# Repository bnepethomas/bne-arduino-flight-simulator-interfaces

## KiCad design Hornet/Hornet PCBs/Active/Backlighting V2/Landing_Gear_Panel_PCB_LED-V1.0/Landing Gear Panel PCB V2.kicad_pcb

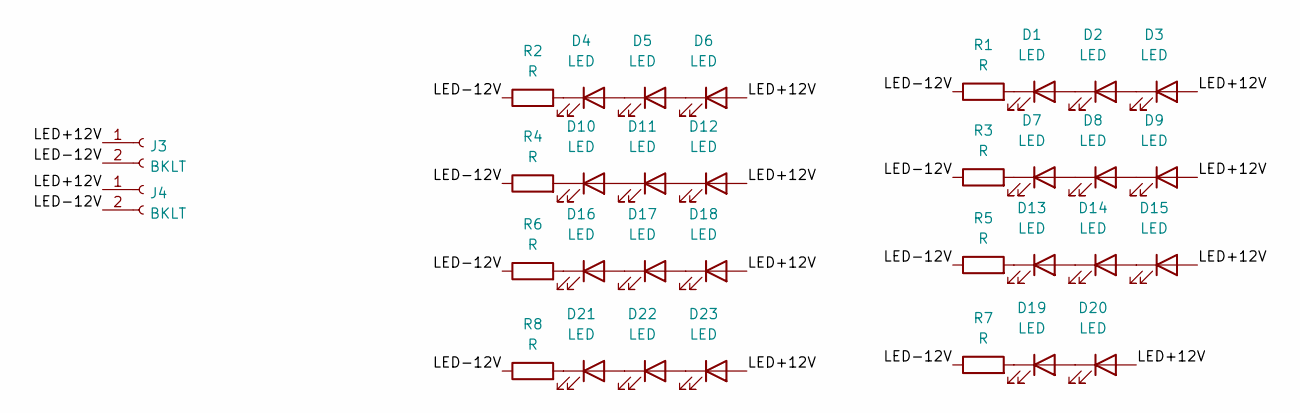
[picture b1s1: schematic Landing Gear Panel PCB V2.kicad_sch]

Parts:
D1, D2, D3, D4, D5, D6, D7, D8, D9, D10, D11, D12, D13, D14, D15, D16, D17, D18, D19, D20, D21, D22, D23: LED; LED_D3.0mm
J3, J4: BKLT; Molex_KK-254_AE-6410-02A_1x02_P2.54mm_Vertical
R1, R2, R3, R4, R5, R6, R7, R8: R; R_Axial_DIN0204_L3.6mm_D1.6mm_P2.54mm_Vertical

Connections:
/LED+12V: D3.2 (A), D6.2 (A), D9.2 (A), D12.2 (A), D15.2 (A), D18.2 (A), D20.2 (A), D23.2 (A), J3.1, J4.1
/LED-12V: J3.2, J4.2, R1.1, R2.1, R3.1, R4.1, R5.1, R6.1, R7.1, R8.1
unnamed: D1.1 (K), R1.2
unnamed: D1.2 (A), D2.1 (K)
unnamed: D2.2 (A), D3.1 (K)
unnamed: D4.1 (K), R2.2
unnamed: D4.2 (A), D5.1 (K)
unnamed: D5.2 (A), D6.1 (K)
unnamed: D7.1 (K), R3.2
unnamed: D7.2 (A), D8.1 (K)
unnamed: D8.2 (A), D9.1 (K)
unnamed: D10.1 (K), R4.2
unnamed: D10.2 (A), D11.1 (K)
unnamed: D11.2 (A), D12.1 (K)
unnamed: D13.1 (K), R5.2
unnamed: D13.2 (A), D14.1 (K)
unnamed: D14.2 (A), D15.1 (K)
unnamed: D16.1 (K), R6.2
unnamed: D16.2 (A), D17.1 (K)
unnamed: D17.2 (A), D18.1 (K)
unnamed: D19.1 (K), R7.2
unnamed: D19.2 (A), D20.1 (K)
unnamed: D21.1 (K), R8.2
unnamed: D21.2 (A), D22.1 (K)
unnamed: D22.2 (A), D23.1 (K)

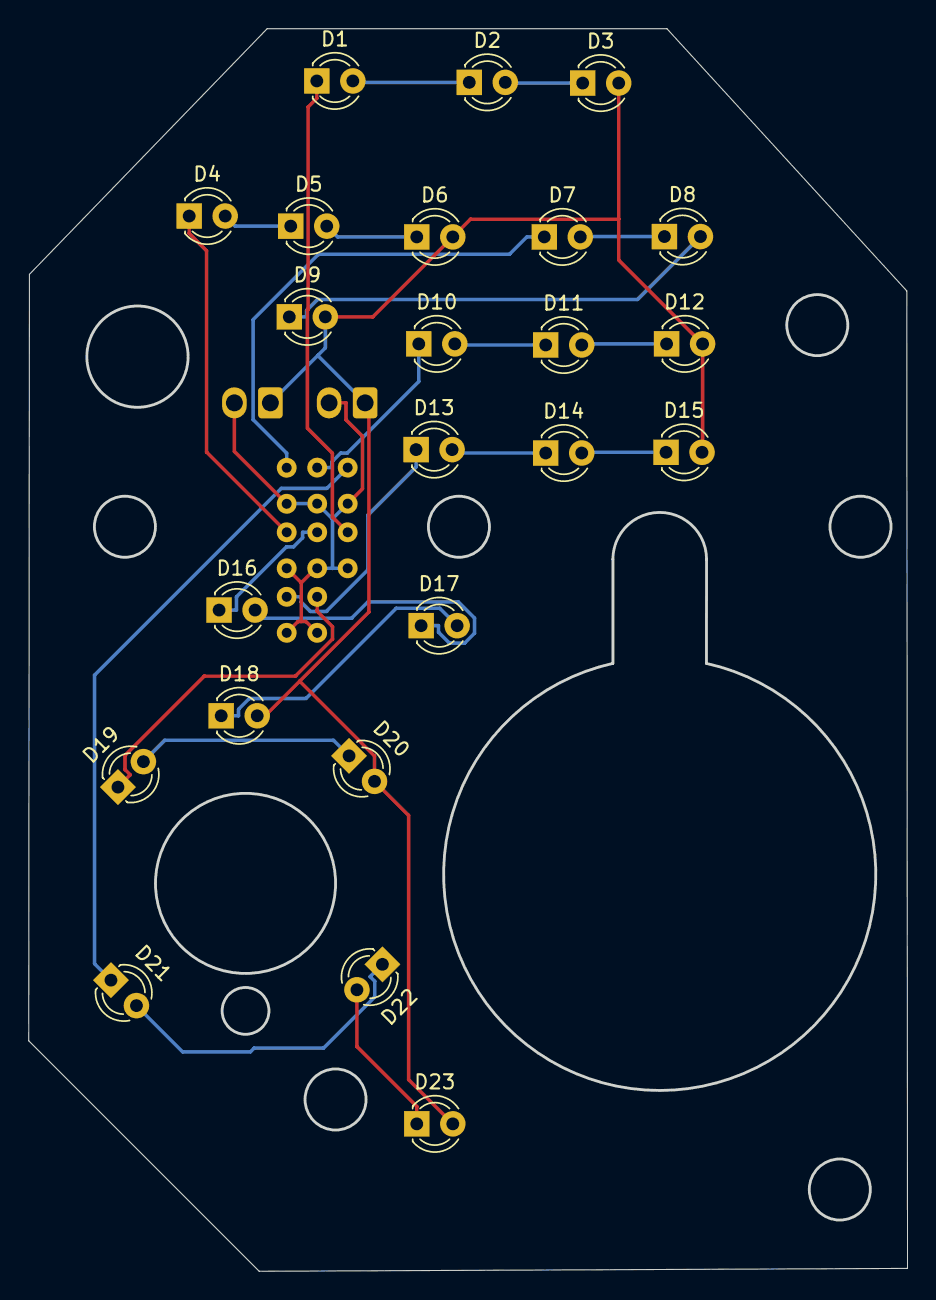
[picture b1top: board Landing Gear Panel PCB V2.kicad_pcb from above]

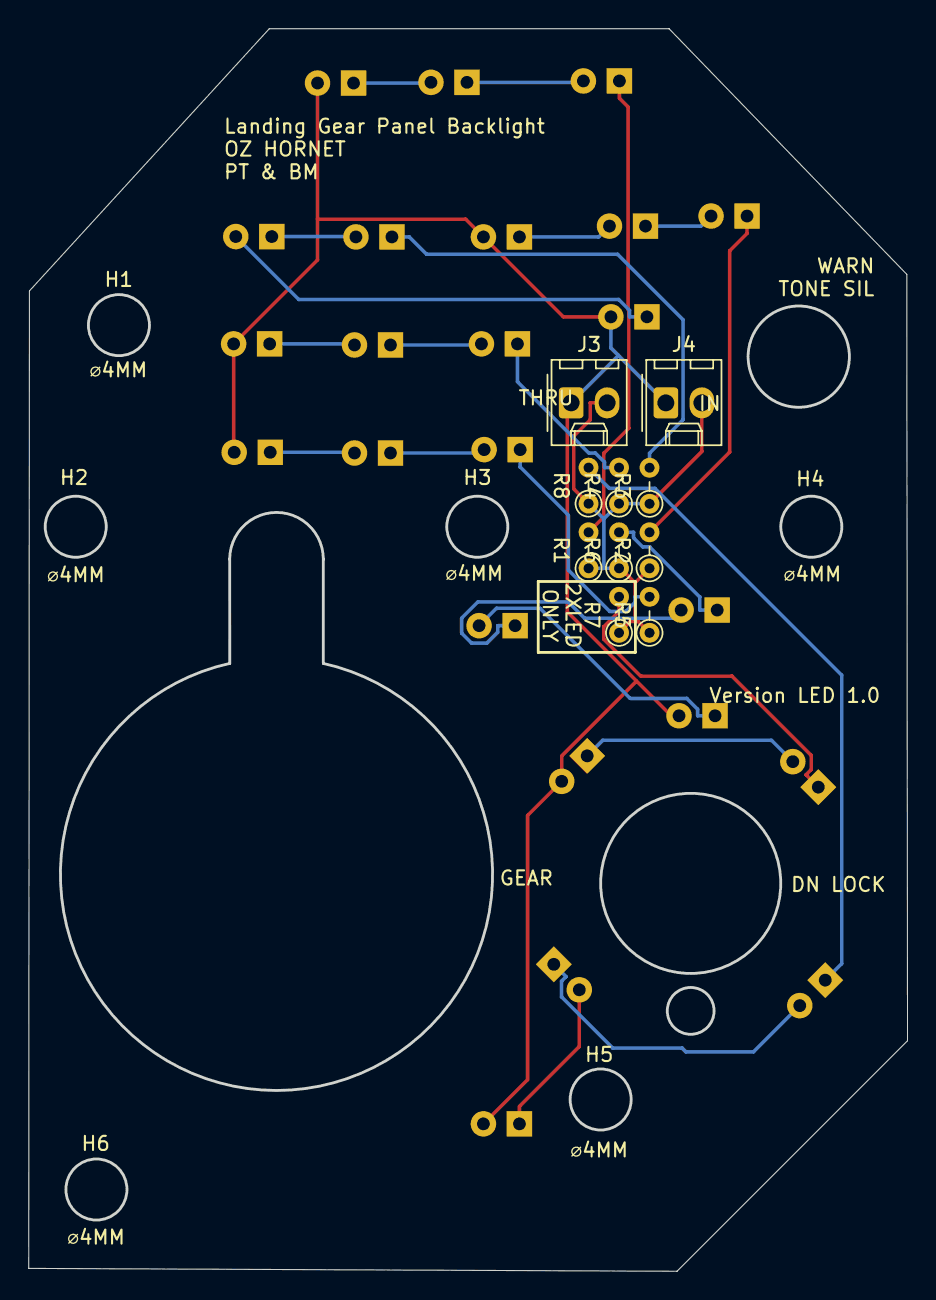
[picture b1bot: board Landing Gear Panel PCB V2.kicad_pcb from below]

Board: 2 copper layers, 62.0 x 87.6 mm, 33 parts (10 on the bottom side), 25 nets.

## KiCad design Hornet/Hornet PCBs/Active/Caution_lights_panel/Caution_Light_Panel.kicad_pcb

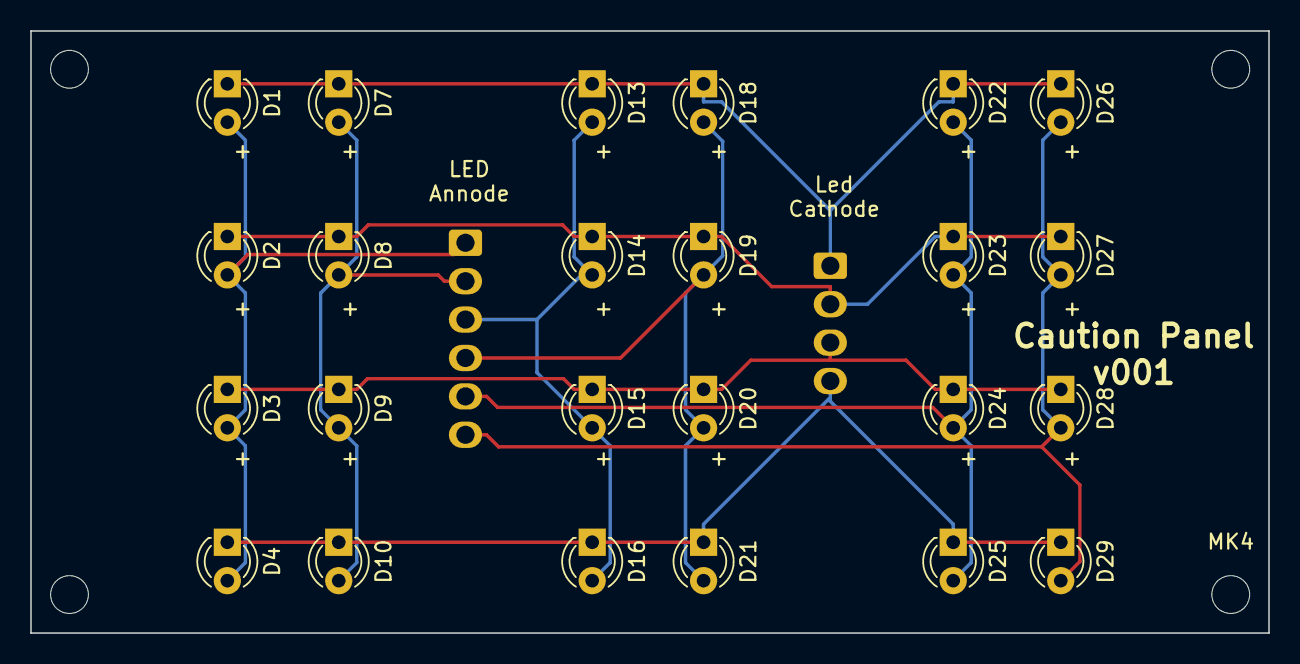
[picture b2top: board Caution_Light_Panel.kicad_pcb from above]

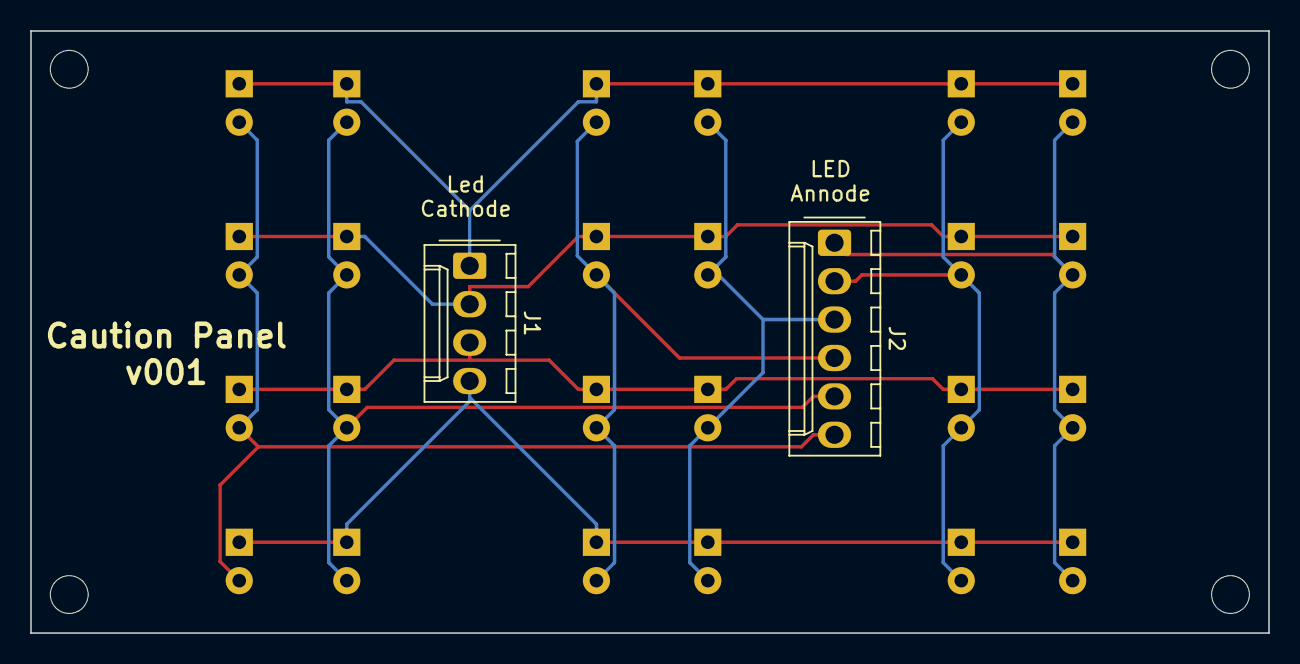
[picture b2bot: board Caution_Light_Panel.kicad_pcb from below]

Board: 2 copper layers, 81.9 x 39.8 mm, 30 parts (2 on the bottom side), 10 nets.

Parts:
D1: 0,0; LED_D3.0mm_FlatTop
D2: 1,0; LED_D3.0mm_FlatTop
D3: 2,0; LED_D3.0mm_FlatTop
D4: 3,0; LED_D3.0mm_FlatTop
D7: 0,1; LED_D3.0mm_FlatTop
D8: 1,1; LED_D3.0mm_FlatTop
D9: 2,1; LED_D3.0mm_FlatTop
D10: 3,1; LED_D3.0mm_FlatTop
D13: 0,2; LED_D3.0mm_FlatTop
D14: 1,2; LED_D3.0mm_FlatTop
D15: 2,2; LED_D3.0mm_FlatTop
D16: 3,2; LED_D3.0mm_FlatTop
D18: 0,3; LED_D3.0mm_FlatTop
D19: 1.3; LED_D3.0mm_FlatTop
D20: 2,3; LED_D3.0mm_FlatTop
D21: 3,3; LED_D3.0mm_FlatTop
D22: 0.4; LED_D3.0mm_FlatTop
D23: 1.4; LED_D3.0mm_FlatTop
D24: 2,4; LED_D3.0mm_FlatTop
D25: 3,4; LED_D3.0mm_FlatTop
D26: 0.5; LED_D3.0mm_FlatTop
D27: 1.5; LED_D3.0mm_FlatTop
D28: 2,5; LED_D3.0mm_FlatTop
D29: 3,5; LED_D3.0mm_FlatTop
J1: LedCathode; Molex_1x04_P2.54mm_Vertical
J2: LEDAnnode; Molex_1x06_P2.54mm_Vertical
MK1, MK2, MK3, MK4: Mounting_Hole; MountingHole_2.5mm

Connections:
/Dig0: D1.1, D7.1, D13.1, D18.1, D22.1, D26.1, J1.1
/Dig1: D2.1, D8.1, D14.1, D19.1, D23.1, D27.1, J1.2
/Dig2: D3.1, D9.1, D15.1, D20.1, D24.1, D28.1, J1.3
/Dig3: D4.1, D10.1, D16.1, D21.1, D25.1, D29.1, J1.4
/SegA: D7.2, D8.2, D9.2, D10.2, J2.2
/SegB: D13.2, D14.2, D15.2, D16.2, J2.3
/SegC: D18.2, D19.2, D20.2, D21.2, J2.4
/SegD: D22.2, D23.2, D24.2, D25.2, J2.5
/SegDP: D1.2, D2.2, D3.2, D4.2, J2.1
/SegE: D26.2, D27.2, D28.2, D29.2, J2.6

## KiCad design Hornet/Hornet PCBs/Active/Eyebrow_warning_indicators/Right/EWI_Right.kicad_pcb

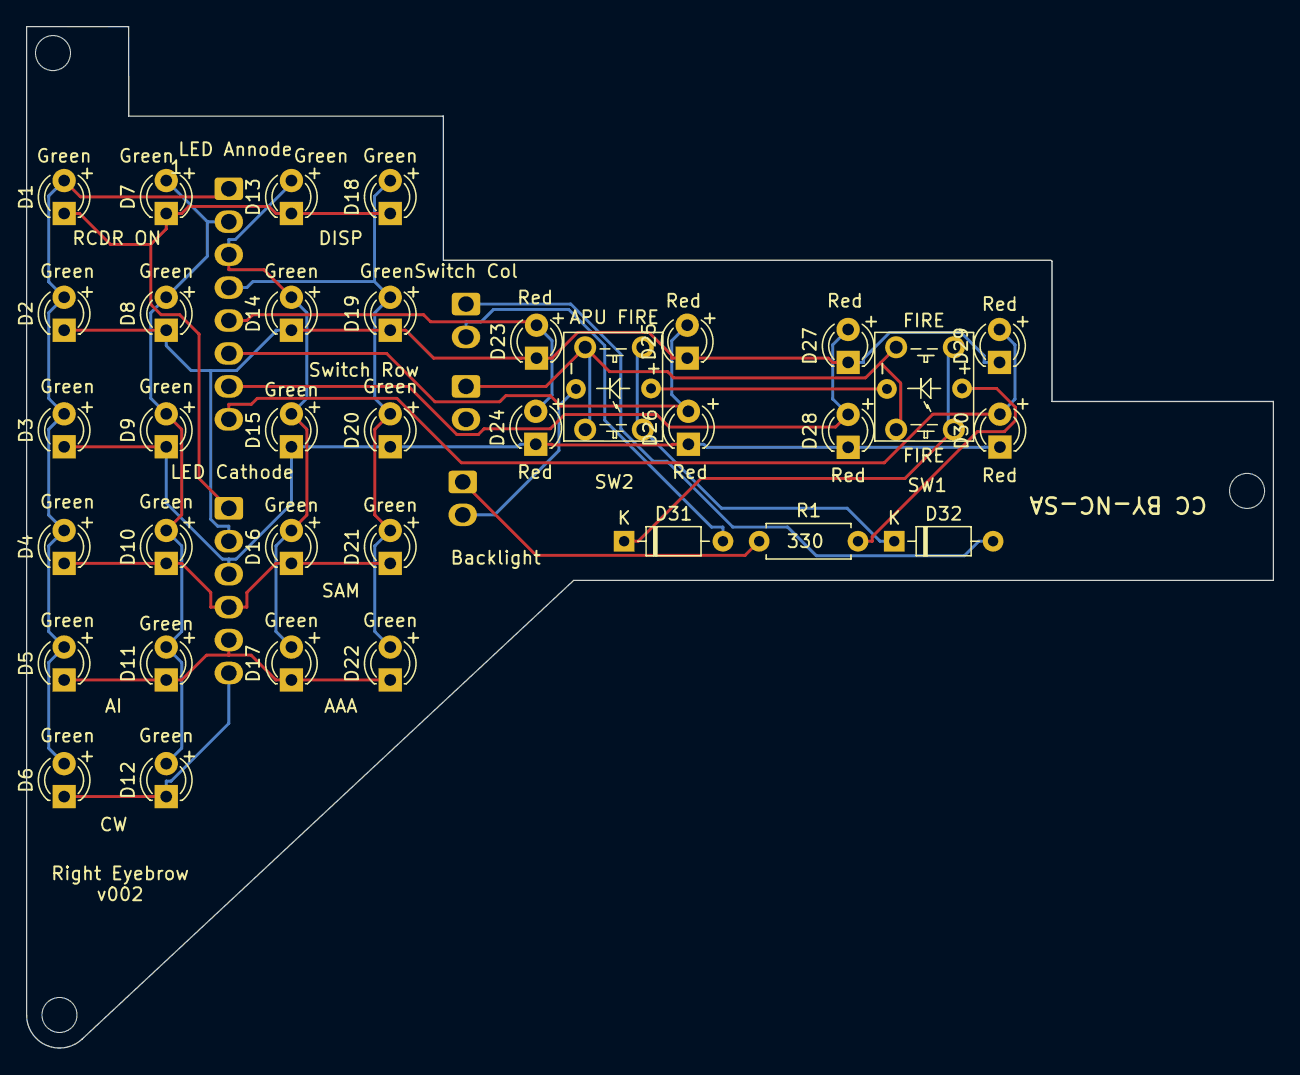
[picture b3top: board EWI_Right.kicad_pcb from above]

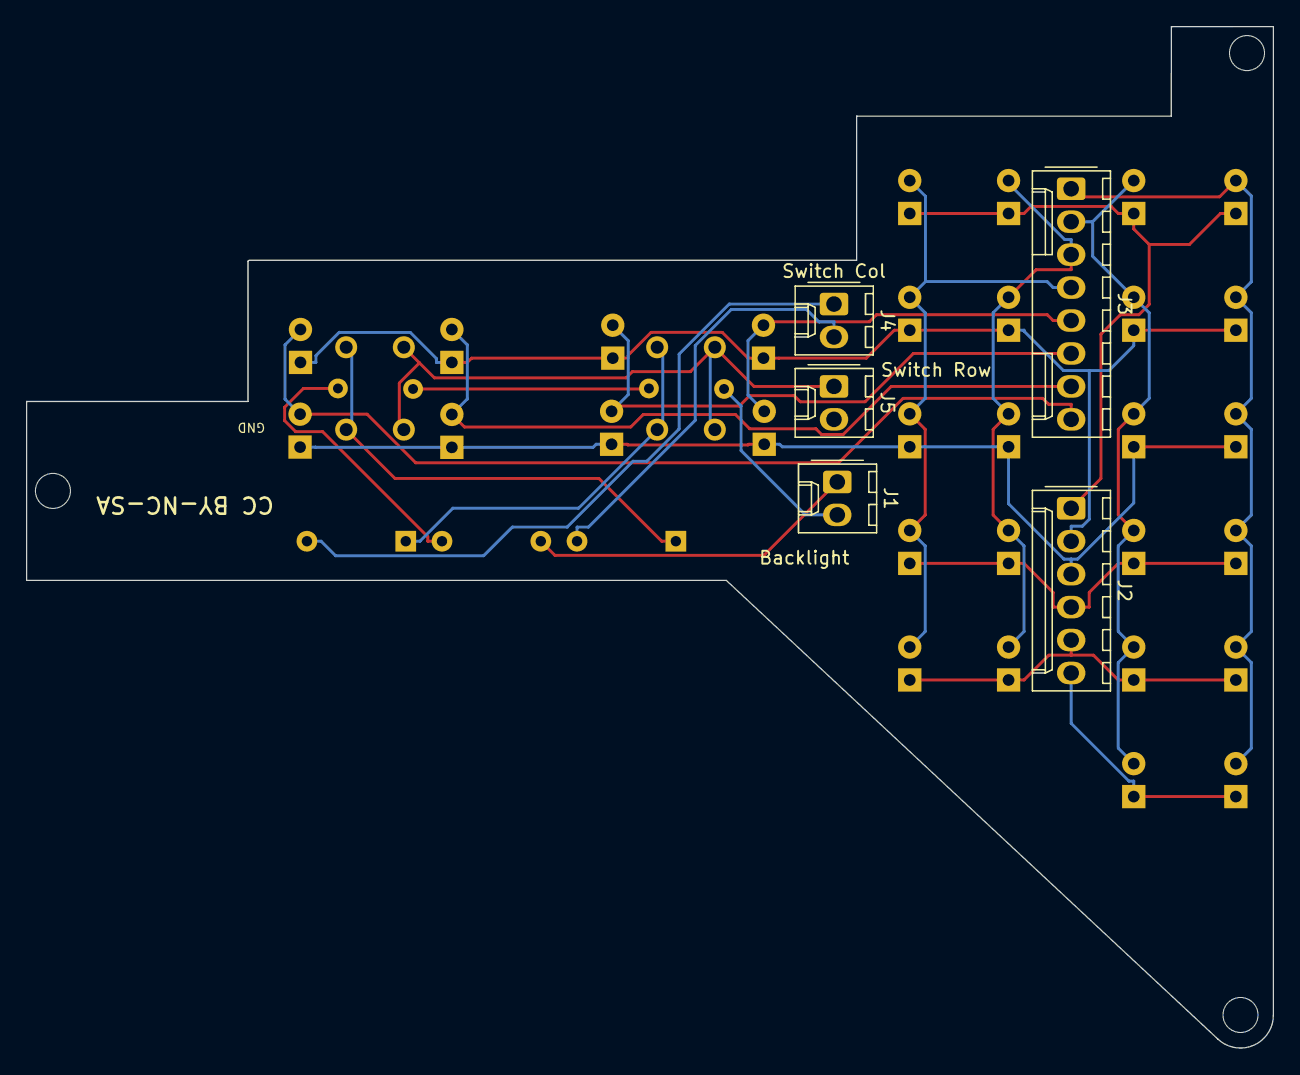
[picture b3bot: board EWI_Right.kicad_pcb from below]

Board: 2 copper layers, 96.1 x 78.8 mm, 43 parts (8 on the bottom side), 23 nets.

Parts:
D1: 0,0; LED_D3.0mm_FlatTop
D2: 1,0; LED_D3.0mm_FlatTop
D3: 2,0; LED_D3.0mm_FlatTop
D4: 3,0; LED_D3.0mm_FlatTop
D5: 4,0; LED_D3.0mm_FlatTop
D6: 5,0; LED_D3.0mm_FlatTop
D7: 0,1; LED_D3.0mm_FlatTop
D8: 1,1; LED_D3.0mm_FlatTop
D9: 2,1; LED_D3.0mm_FlatTop
D10: 3,1; LED_D3.0mm_FlatTop
D11: 4,1; LED_D3.0mm_FlatTop
D12: 5,1; LED_D3.0mm_FlatTop
D13: 0,2; LED_D3.0mm_FlatTop
D14: 1,2; LED_D3.0mm_FlatTop
D15: 2,2; LED_D3.0mm_FlatTop
D16: 3,2; LED_D3.0mm_FlatTop
D17: 4,2; LED_D3.0mm_FlatTop
D18: 0,3; LED_D3.0mm_FlatTop
D19: 1.3; LED_D3.0mm_FlatTop
D20: 2,3; LED_D3.0mm_FlatTop
D21: 3,3; LED_D3.0mm_FlatTop
D22: 4,3; LED_D3.0mm_FlatTop
D23: 1.4; LED_D3.0mm_FlatTop
D24: 2,4; LED_D3.0mm_FlatTop
D25: 1.5; LED_D3.0mm_FlatTop
D26: 2,5; LED_D3.0mm_FlatTop
D27: 1.6; LED_D3.0mm_FlatTop
D28: 2,6; LED_D3.0mm_FlatTop
D29: 1.7; LED_D3.0mm_FlatTop
D30: 2,7; LED_D3.0mm_FlatTop
D31, D32: D; D_Signal_P7.62mm_Horizontal
J1: Backlight; Molex_1x02_P2.54mm_Vertical
J2: Led Cathode; Molex_1x06_P2.54mm_Vertical
J3: Led Annode; Molex_1x08_P2.54mm_Vertical
J4: SwitchCol; Molex_1x02_P2.54mm_Vertical
J5: SwitchRow; Molex_1x02_P2.54mm_Vertical
MK1, MK2, MK3: Mounting_Hole; MountingHole_2.7mm_M2.5_ISO14580
R1: 330; R_Axial_DIN0207_L6.3mm_D2.5mm_P7.62mm_Horizontal
SW1: IN SWTCH; PT_Small_Tactile_Switch_With_LED
SW2: OUT SWTCH; PT_Small_Tactile_Switch_With_LED

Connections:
/Dig0: D1.1, D7.1, D13.1, D18.1, J2.1
/Dig1: D2.1, D8.1, D14.1, D19.1, D23.1, D25.1, D27.1, D29.1, J2.2
/Dig2: D3.1, D9.1, D15.1, D20.1, D24.1, D26.1, D28.1, D30.1, J2.3
/Dig3: D4.1, D10.1, D16.1, D21.1, J2.4
/Dig4: D5.1, D11.1, D17.1, D22.1, J2.5
/Dig5: D6.1, D12.1, J2.6
/SegA: D7.2, D8.2, D9.2, D10.2, D11.2, D12.2, J3.2
/SegB: D13.2, D14.2, D15.2, D16.2, D17.2, J3.3
/SegC: D18.2, D19.2, D20.2, D21.2, D22.2, J3.4
/SegD: D23.2, D24.2, J3.5
/SegDP: D1.2, D2.2, D3.2, D4.2, D5.2, D6.2, J3.1
/SegE: D25.2, D26.2, J3.6
/SegF: D27.2, D28.2, J3.7
/SegG: D29.2, D30.2, J3.8
unnamed: D31.1, SW1.1, SW1.2
unnamed: D31.2, J4.2
unnamed: D32.1, SW2.1, SW2.2
unnamed: D32.2, J4.1
unnamed: J1.1, R1.1
unnamed: J1.2, SW2.6
unnamed: J5.1, SW1.3, SW1.4, SW2.3, SW2.4
unnamed: R1.2, SW1.5
unnamed: SW1.6, SW2.5

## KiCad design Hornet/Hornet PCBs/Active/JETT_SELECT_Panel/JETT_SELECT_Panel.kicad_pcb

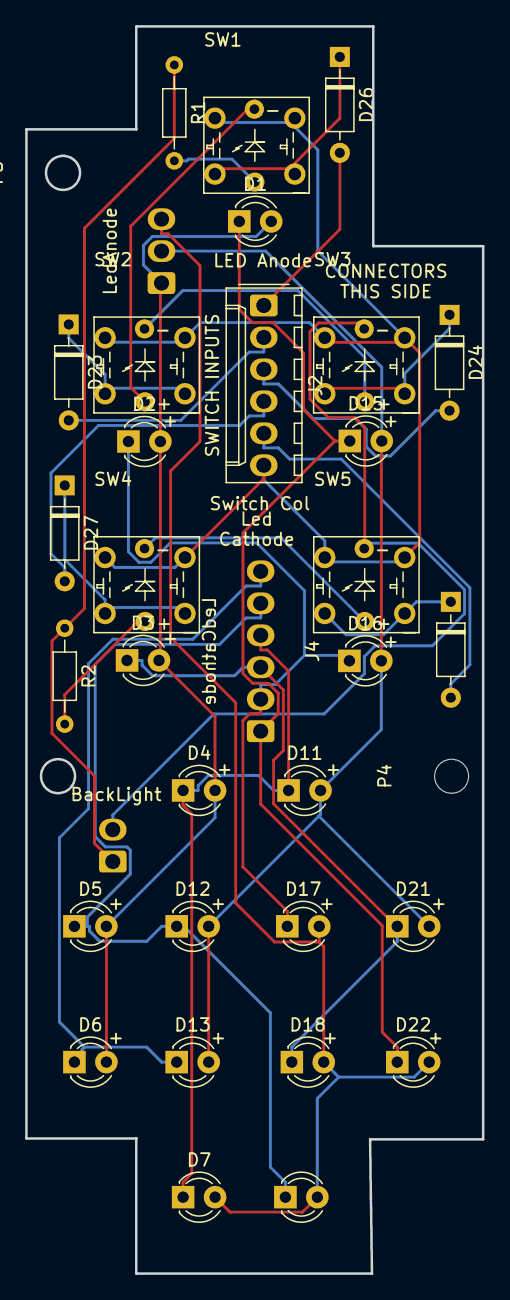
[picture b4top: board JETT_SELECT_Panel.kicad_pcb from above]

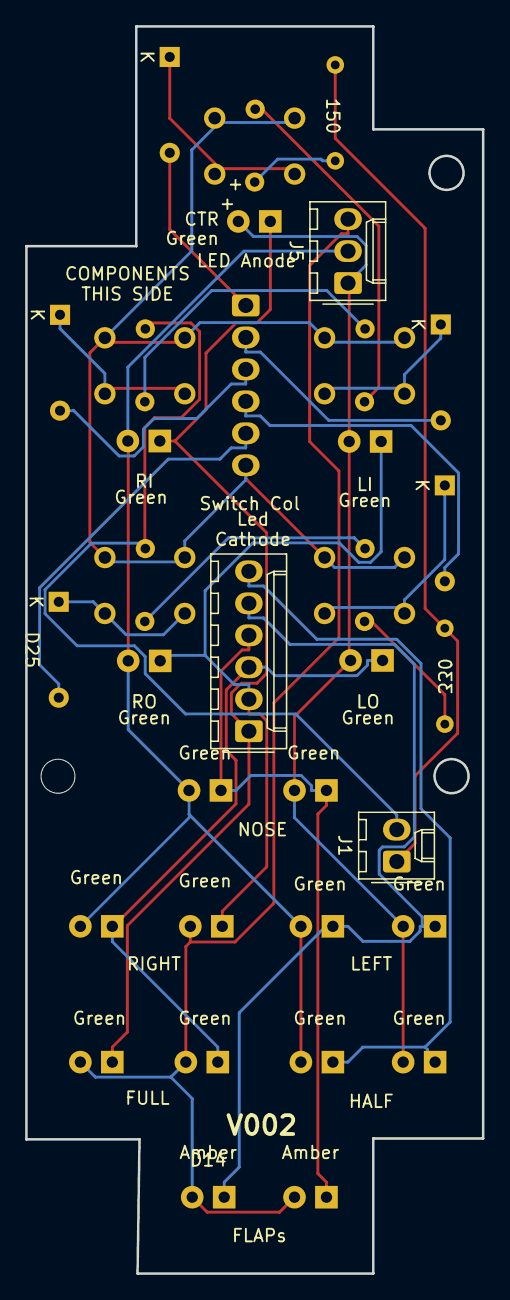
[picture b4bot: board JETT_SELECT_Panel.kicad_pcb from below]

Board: 2 copper layers, 36.3 x 99.1 mm, 35 parts (3 on the bottom side), 27 nets.

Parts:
D1: 0,0; LED_D3.0mm_Clear
D2: 1,0; LED_D3.0mm_Clear
D3: 2,0; LED_D3.0mm_Clear
D4: 3,0; LED_D3.0mm_Clear
D5: 4,0; LED_D3.0mm_Clear
D6: 5,0; LED_D3.0mm_Clear
D7: 6,0; LED_D3.0mm_Clear
D11: 3,1; LED_D3.0mm_Clear
D12: 4,1; LED_D3.0mm_Clear
D13: 5,1; LED_D3.0mm_Clear
D14: 6,1; LED_D3.0mm_Clear
D15: 1,2; LED_D3.0mm_Clear
D16: 2,2; LED_D3.0mm_Clear
D17: 4,2; LED_D3.0mm_Clear
D18: 5,2; LED_D3.0mm_Clear
D21: 4,3; LED_D3.0mm_Clear
D22: 5,3; LED_D3.0mm_Clear
D23, D24, D25, D26, D27: D; D_Signal_P7.62mm_Horizontal
J1: BackLight; Molex_1x02_P2.54mm_Vertical
J2: SWITCH INPUTS; Molex_1x06_P2.54mm_Vertical
J4: LedCathode; Molex_1x06_P2.54mm_Vertical
J5: LedAnode; Molex_1x03_P2.54mm_Vertical
P3, P4: CONN_01X01; MountingHole_2.7mm_M2.5
R1: 150; R_Axial_DIN0204_L3.6mm_D1.6mm_P7.62mm_Horizontal
R2: 330; R_Axial_DIN0204_L3.6mm_D1.6mm_P7.62mm_Horizontal
SW1, SW2, SW3, SW4, SW5: SW_Push; PT_Small_Tactile_Switch_With_LED

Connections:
/COL6: D26.2, J2.1
/COL7: D23.2, J2.2
/COL8: D24.2, J2.3
/COL9: D27.2, J2.4
/COL10: D25.2, J2.5
/Dig0: D1.1, D15.1, D22.1, J4.1
/Dig1: D2.1, D16.1, D17.1, J4.2
/Dig2: D3.1, D18.1, D21.1, J4.3
/Dig3: D4.1, D7.1, D11.1, J4.4
/Dig4: D5.1, D12.1, D14.1, J4.5
/Dig5: D6.1, D13.1, J4.6
/ROW15: J2.6, SW1.3, SW1.4, SW2.3, SW2.4, SW3.3, SW3.4, SW4.3, SW4.4, SW5.3, SW5.4
/SegA: D11.2, D12.2, D13.2, D15.2, D16.2, D21.2, J5.2
/SegB: D7.2, D14.2, D17.2, D18.2, D22.2, J5.3
/SegDP: D1.2, D2.2, D3.2, D4.2, D5.2, D6.2, J5.1
unnamed: D23.1, SW2.1, SW2.2
unnamed: D24.1, SW3.1, SW3.2
unnamed: D25.1, SW5.1, SW5.2
unnamed: D26.1, SW1.1, SW1.2
unnamed: D27.1, SW4.1, SW4.2
unnamed: J1.1, R1.1, R2.1
unnamed: J1.2, SW3.6, SW5.6
unnamed: R1.2, SW1.5
unnamed: R2.2, SW4.5
unnamed: SW1.6, SW2.5
unnamed: SW2.6, SW3.5
unnamed: SW4.6, SW5.5

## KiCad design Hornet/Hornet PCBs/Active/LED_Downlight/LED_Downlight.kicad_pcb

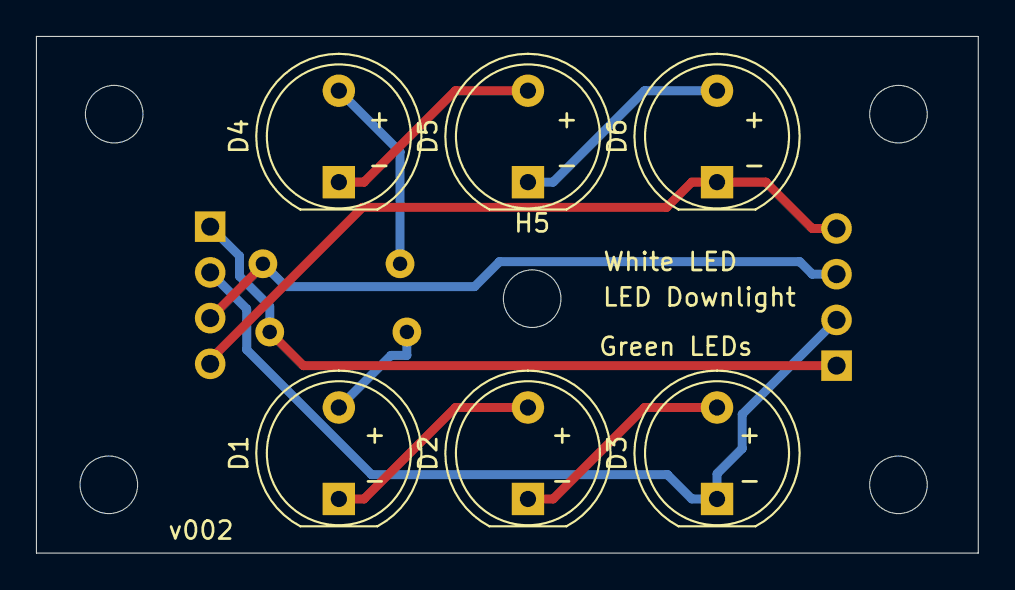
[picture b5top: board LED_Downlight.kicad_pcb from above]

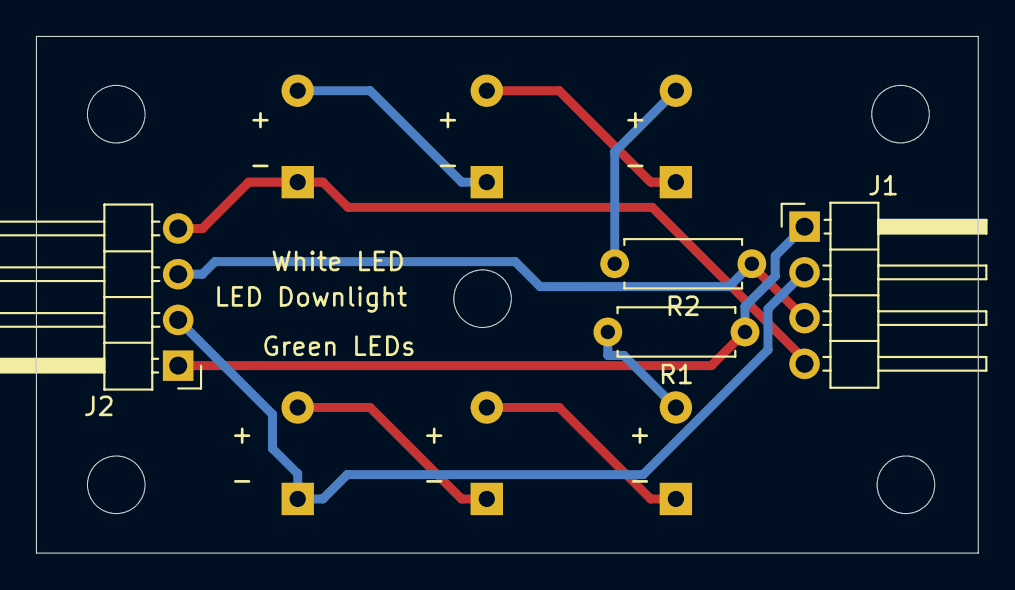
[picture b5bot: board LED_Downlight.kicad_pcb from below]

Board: 2 copper layers, 52.3 x 28.7 mm, 15 parts (4 on the bottom side), 10 nets.

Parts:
D1, D2, D3, D4, D5, D6: LED; LED_D8.0mm-LargePins
H1, H2, H3, H4, H5: MountingHole; MountingHole_3.2mm_M3
J1, J2: Conn_01x04_Female; PinHeader_1x04_P2.54mm_Horizontal
R1, R2: R_US; R_Axial_DIN0207_L6.3mm_D2.5mm_P7.62mm_Horizontal

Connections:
/+12VGreen: J1.1, J2.1, R1.1
/+12VWhite: J1.3, J2.3, R2.1
/GNDGreen: D3.1, J1.2, J2.2
/GNDWhite: D6.1, J1.4, J2.4
unnamed: D1.1, D2.2
unnamed: D1.2, R1.2
unnamed: D2.1, D3.2
unnamed: D4.1, D5.2
unnamed: D4.2, R2.2
unnamed: D5.1, D6.2

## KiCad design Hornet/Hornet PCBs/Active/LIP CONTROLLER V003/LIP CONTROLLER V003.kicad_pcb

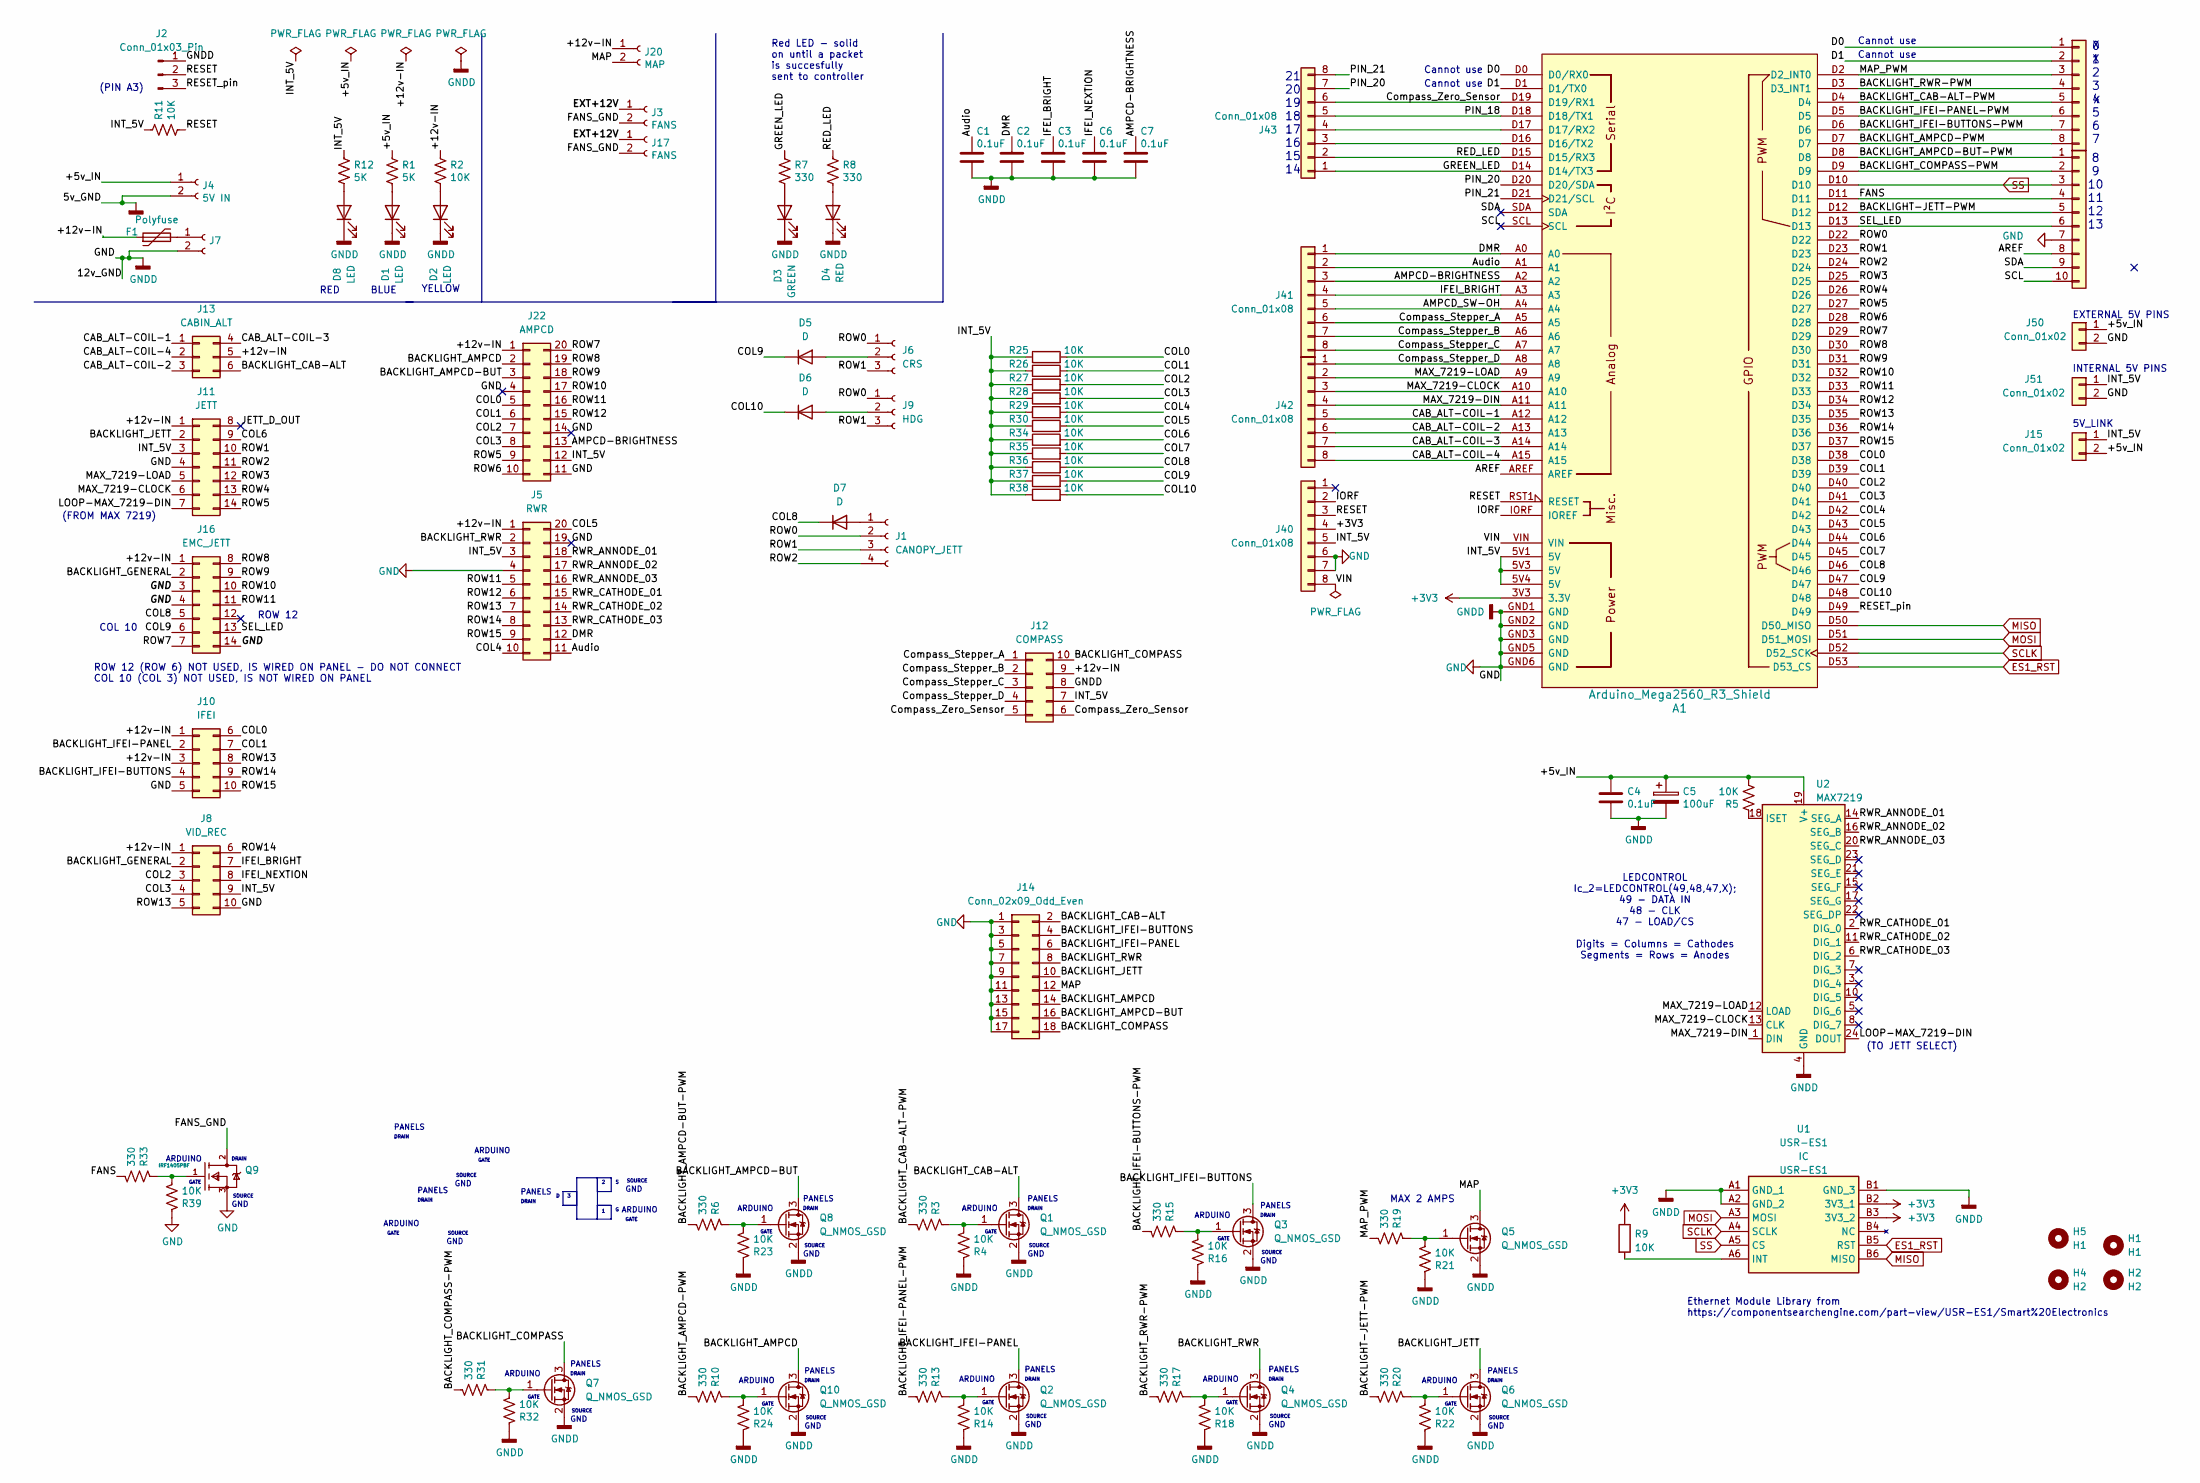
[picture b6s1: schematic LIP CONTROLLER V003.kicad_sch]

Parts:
A1: Arduino_Mega2560_R3_Shield
C1, C2, C3, C4, C6, C7: 0.1uF; C_0805_2012Metric
C5: 100uF; C_1210_3225Metric
D1, D2, D8: LED; LED_0805_2012Metric
D3: GREEN; LED_0805_2012Metric
D4: RED; LED_0805_2012Metric
D5, D6, D7: D; D_0805_2012Metric
F1: Polyfuse; Fuse_1206_3216Metric
H1, H5: H1; MountingHole_2.5mm
H2, H4: H2; MountingHole_2.5mm
J1: CANOPY_JETT; JST_XA_B04B-XASK-1_1x04_P2.50mm_Vertical
J2: Conn_01x03_Pin; PinHeader_1x03_P2.54mm_Vertical
J3, J17: FANS; Molex_KK-254_AE-6410-02A_1x02_P2.54mm_Vertical
J4: 5V IN; BarrelJack_Horizontal
J5: RWR; IDC-Header_2x10_P2.54mm_Vertical
J6: CRS; JST_XA_B03B-XASK-1_1x03_P2.50mm_Vertical
J7: STEPPER IN 12-20VDC; BarrelJack_Horizontal
J8: VID_REC; IDC-Header_2x05_P2.54mm_Vertical
J9: HDG; JST_XA_B03B-XASK-1_1x03_P2.50mm_Vertical
J10: IFEI; IDC-Header_2x05_P2.54mm_Vertical
J11: JETT; IDC-Header_2x07_P2.54mm_Vertical
J12: COMPASS; IDC-Header_2x05_P2.54mm_Vertical
J13: CABIN_ALT; IDC-Header_2x03_P2.54mm_Vertical
J14: Conn_02x09_Odd_Even; PinHeader_2x09_P2.54mm_Vertical
J15, J50, J51: Conn_01x02; PinHeader_1x02_P2.54mm_Vertical
J16: EMC_JETT; IDC-Header_2x07_P2.54mm_Vertical
J20: MAP; Molex_KK-254_AE-6410-02A_1x02_P2.54mm_Vertical
J22: AMPCD; IDC-Header_2x10_P2.54mm_Vertical
J40, J41, J42, J43, J44: Conn_01x08; PinHeader_1x08_P2.54mm_Vertical
J45: Conn_01x10; PinHeader_1x10_P2.54mm_Vertical
Q1, Q2, Q3, Q4, Q5, Q6, Q7, Q8, Q10: Q_NMOS_GSD; SOT-23
Q9: IRF1405PBF; TO-220-3_Vertical; mouser part number 942-IRF1405PBF; digikey description MOSFET N-CH 55V 169A TO-220AB
R1, R12: 5K; R_0805_2012Metric
R2, R4, R5, R9, R11, R14, R16, R18, R21, R22, R23, R24, R25, R26, R27, R28, R29, R30, R32, R34, R35, R36, R37, R38, R39: 10K; R_0805_2012Metric
R3, R6, R7, R8, R10, R13, R15, R17, R19, R20, R31, R33: 330; R_0805_2012Metric
U1: USR-ES1; USRES1; Manufacturer_Part_Number USR-ES1
U2: MAX7219; DIP-24_W7.62mm_LongPads

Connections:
+3V3: A1.3V3 (3.3V), J40.4, R9.1, U1.B2 (3V3_1), U1.B3 (3V3_2)
/+5v_IN: C4.1, C5.1, J4.1, J15.2, J50.1, R1.1, R5.2, U2.19 (V+)
/+12v-IN: F1.1, J5.1, J8.1, J10.1, J10.3, J11.1, J12.9, J13.5, J16.1, J20.1, J22.1, R2.1
/AMPCD-BRIGHTNESS: A1.A2, C7.1, J22.13, J41.3
/AMPCD_SW-OH: A1.A4, J41.5
/AREF: A1.AREF, J45.8
/Audio: A1.A1, C1.1, J5.11, J41.2
/BACKLIGHT-JETT-PWM: A1.D12, J45.5, R20.2
/BACKLIGHT_AMPCD: J14.14, J22.2, Q10.3 (D)
/BACKLIGHT_AMPCD-BUT: J14.16, J22.3, Q8.3 (D)
/BACKLIGHT_AMPCD-BUT-PWM: A1.D8, J45.1, R6.2
/BACKLIGHT_AMPCD-PWM: A1.D7, J44.8, R10.2
/BACKLIGHT_CAB-ALT: J13.6, J14.2, Q1.3 (D)
/BACKLIGHT_CAB-ALT-PWM: A1.D4, J44.5, R3.2
/BACKLIGHT_COMPASS: J12.10, J14.18, Q7.3 (D)
/BACKLIGHT_COMPASS-PWM: A1.D9, J45.2, R31.2
/BACKLIGHT_GENERAL: J8.2, J16.2
/BACKLIGHT_IFEI-BUTTONS: J10.4, J14.4, Q3.3 (D)
/BACKLIGHT_IFEI-BUTTONS-PWM: A1.D6, J44.7, R15.2
/BACKLIGHT_IFEI-PANEL: J10.2, J14.6, Q2.3 (D)
/BACKLIGHT_IFEI-PANEL-PWM: A1.D5, J44.6, R13.2
/BACKLIGHT_JETT: J11.2, J14.10, Q6.3 (D)
/BACKLIGHT_RWR: J5.2, J14.8, Q4.3 (D)
/BACKLIGHT_RWR-PWM: A1.D3 (D3_INT1), J44.4, R17.2
/CAB_ALT-COIL-1: A1.A12, J13.1, J42.5
/CAB_ALT-COIL-2: A1.A13, J13.3, J42.6
/CAB_ALT-COIL-3: A1.A14, J13.4, J42.7
/CAB_ALT-COIL-4: A1.A15, J13.2, J42.8
/COL0: A1.D38, J10.6, J22.5, R25.2
/COL1: A1.D39, J10.7, J22.6, R26.2
/COL2: A1.D40, J8.3, J22.7, R27.2
/COL3: A1.D41, J8.4, J22.8, R28.2
/COL4: A1.D42, J5.10, R29.2
/COL5: A1.D43, J5.20, R30.2
/COL6: A1.D44, J11.9, R34.2
/COL7: A1.D45, R35.2
/COL8: A1.D46, D7.1 (K), J16.5, R36.2
/COL9: A1.D47, D5.1 (K), J16.6, R37.2
/COL10: A1.D48, D6.1 (K), R38.2
/Compass_Stepper_A: A1.A5, J12.1, J41.6
/Compass_Stepper_B: A1.A6, J12.2, J41.7
/Compass_Stepper_C: A1.A7, J12.3, J41.8
/Compass_Stepper_D: A1.A8, J12.4, J42.1
/Compass_Zero_Sensor: A1.D19 (D19/RX1), J12.5, J12.6, J43.6
/D0: A1.D0 (D0/RX0), J44.1
/D1: A1.D1 (D1/TX0), J44.2
/DMR: A1.A0, C2.1, J5.12, J41.1
/EXT+12V: J3.1, J17.1
/FANS: A1.D11, J45.4, R33.2
/FANS_GND: J3.2, J17.2, Q9.2 (D)
/GREEN_LED: A1.D14 (D14/TX3), J43.1, R7.1
/IFEI_BRIGHT: A1.A3, C3.1, J8.7, J41.4
/IFEI_NEXTION: C6.1, J8.8
/INT_5V: A1.5V1 (5V), A1.5V3 (5V), A1.5V4 (5V), J5.3, J8.9, J11.3, J12.7, J15.1, J22.12, J40.5, J51.1, R11.1, R12.1, R25.1, R26.1, R27.1, R28.1, R29.1, R30.1, R34.1, R35.1, R36.1, R37.1, R38.1
/IORF: A1.IORF (IOREF), J40.2
/JETT_D_OUT: J11.8
/LOOP-MAX_7219-DIN: J11.7, U2.24 (DOUT)
/MAP: J14.12, J20.2, Q5.3 (D)
/MAP_PWM: A1.D2 (D2_INT0), J44.3, R19.2
/MAX_7219-CLOCK: A1.A10, J11.6, J42.3, U2.13 (CLK)
/MAX_7219-DIN: A1.A11, J42.4, U2.1 (DIN)
/MAX_7219-LOAD: A1.A9, J11.5, J42.2, U2.12 (LOAD)
/PIN_18: A1.D18 (D18/TX1), J43.5
/PIN_20: A1.D20 (D20/SDA), J43.7
/PIN_21: A1.D21 (D21/SCL), J43.8
/RED_LED: A1.D15 (D15/RX3), J43.2, R8.1
/RESET: A1.RST1 (RESET), J2.2, J40.3, R11.2
/RESET_pin: A1.D49, J2.3
/ROW0: A1.D22, J1.2, J6.1, J9.1
/ROW1: A1.D23, J1.3, J6.3, J9.3, J11.10
/ROW2: A1.D24, J1.4, J11.11
/ROW3: A1.D25, J11.12
/ROW4: A1.D26, J11.13
/ROW5: A1.D27, J11.14, J22.9
/ROW6: A1.D28, J22.10
/ROW7: A1.D29, J16.7, J22.20
/ROW8: A1.D30, J16.8, J22.19
/ROW9: A1.D31, J16.9, J22.18
/ROW10: A1.D32, J16.10, J22.17
/ROW11: A1.D33, J5.5, J16.11, J22.16
/ROW12: A1.D34, J5.6, J22.15
/ROW13: A1.D35, J5.7, J8.5, J10.8
/ROW14: A1.D36, J5.8, J8.6, J10.9
/ROW15: A1.D37, J5.9, J10.10
/RWR_ANNODE_01: J5.18, U2.14 (SEG_A)
/RWR_ANNODE_02: J5.17, U2.16 (SEG_B)
/RWR_ANNODE_03: J5.16, U2.20 (SEG_C)
/RWR_CATHODE_01: J5.15, U2.2 (DIG_0)
/RWR_CATHODE_02: J5.14, U2.11 (DIG_1)
/RWR_CATHODE_03: J5.13, U2.6 (DIG_2)
/SCL: A1.SCL, J45.10
/SDA: A1.SDA, J45.9
/SEL_LED: A1.D13, J16.13, J45.6
/VIN: A1.VIN, J40.8
ES1_RST: A1.D53 (D53_CS), U1.B5 (RST)
GND: A1.GND1 (GND), A1.GND2 (GND), A1.GND3 (GND), A1.GND5 (GND), A1.GND6 (GND), C1.2, C2.2, C3.2, C4.2, C5.2, C6.2, C7.2, D1.1 (K), D2.1 (K), D3.1 (K), D4.1 (K), D8.1 (K), J2.1, J4.2, J5.4, J5.19, J7.2, J8.10, J10.5, J11.4, J12.8, J14.1, J14.3, J14.5, J14.7, J14.9, J14.11, J14.13, J14.15, J14.17, J16.3, J16.4, J16.14, J22.4, J22.11, J22.14, J40.6, J40.7, J45.7, J50.2, J51.2, Q1.2 (S), Q2.2 (S), Q3.2 (S), Q4.2 (S), Q5.2 (S), Q6.2 (S), Q7.2 (S), Q8.2 (S), Q9.3 (S), Q10.2 (S), R4.1, R14.1, R16.1, R18.1, R21.1, R22.1, R23.1, R24.1, R32.1, R39.1, U1.A1 (GND_1), U1.A2 (GND_2), U1.B1 (GND_3), U2.4 (GND), U2.9 (GND)
MISO: A1.D50 (D50_MISO), U1.B6 (MISO)
MOSI: A1.D51 (D51_MOSI), U1.A3 (MOSI)
unnamed: A1.D16 (D16/TX2), J43.3
unnamed: A1.D17 (D17/RX2), J43.4
unnamed: D1.2 (A), R1.2
unnamed: D2.2 (A), R2.2
unnamed: D3.2 (A), R7.2
unnamed: D4.2 (A), R8.2
unnamed: D5.2 (A), J6.2
unnamed: D6.2 (A), J9.2
unnamed: D7.2 (A), J1.1
unnamed: D8.2 (A), R12.2
unnamed: F1.2, J7.1
unnamed: Q1.1 (G), R3.1, R4.2
unnamed: Q2.1 (G), R13.1, R14.2
unnamed: Q3.1 (G), R15.1, R16.2
unnamed: Q4.1 (G), R17.1, R18.2
unnamed: Q5.1 (G), R19.1, R21.2
unnamed: Q6.1 (G), R20.1, R22.2
unnamed: Q7.1 (G), R31.1, R32.2
unnamed: Q8.1 (G), R6.1, R23.2
unnamed: Q9.1 (G), R33.1, R39.2
unnamed: Q10.1 (G), R10.1, R24.2
unnamed: R9.2, U1.A6 (INT)
unnamed: R5.1, U2.18 (ISET)
SCLK: A1.D52 (D52_SCK), U1.A4 (SCLK)
SS: A1.D10, J45.3, U1.A5 (CS)

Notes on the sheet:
YELLOW
MAX 2 AMPS
ARDUINO
SOURCE
GATE
COL 10 (COL 3) NOT USED, IS NOT WIRED ON PANEL
PANELS
BLUE
INTERNAL 5V PINS
GND
Ethernet Module Library from https://componentsearchengine.com/part-view/USR-ES1/Smart%20Electronics
LEDCONTROL Ic_2=LEDCONTROL(49,48,47,X); 49 - DATA IN 48 - CLK 47 - LOAD/CS Digits = Columns = Cathodes Segments = Rows = Anodes
DRAIN
Cannot use
RED
(PIN A3)
ROW 12
0 1 2 3 4 5 6 7
Red LED - solid on until a packet is succesfully sent to controller
(FROM MAX 7219)
5V_LINK
ROW 12 (ROW 6) NOT USED, IS WIRED ON PANEL - DO NOT CONNECT
21 20 19 18 17 16 15 14
COL 10
(TO JETT SELECT)
EXTERNAL 5V PINS
8 9 10 11 12 13

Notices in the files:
Hornet/Hornet PCBs/Active/Eyebrow_warning_indicators/Right/EWI_Right.kicad_pcb:
CC BY-NC-SA
Hornet/Hornet PCBs/Active/LIP CONTROLLER V003/LIP CONTROLLER V003.kicad_pcb:
© OZ HORNET
